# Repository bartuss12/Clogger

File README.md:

Clogger — Minimal Linux‑Powered USB eMMC Reader (F1C100S)
Clogger is a tiny, reproducible hardware project built around the Allwinner F1C100S, 
designed to read, clone, and analyze BGA153/BGA169 eMMC chips using nothing more than a Linux system running from an SD card. 
The goal is to create a fully open, hand‑solderable tool that exposes an attached eMMC device to a host PC over USB 
— just like a USB mass‑storage adapter, but built from scratch.

🔧 Goals

*Build a minimal F1C100S board that boots Linux entirely from an SD card

*Provide a UART‑accessible Linux shell for debugging and control

*Use USB gadget mode to expose the connected eMMC as a block device

*Support BGA153/BGA169 eMMC reballing using low‑cost stencils and solder paste

*Offer a fully reproducible Buildroot toolchain (U‑Boot + kernel + rootfs)

*Document the entire bring‑up process: boot flow, device tree, SD layout, and USB configuration

*Create a simple, reliable tool for eMMC backup, cloning, and recovery

29.12.2025 Work on first hardware version started

31.12.2025 Added 3D models, added LEDs (for work without terminal), added decoupling capacitors, added line resistors

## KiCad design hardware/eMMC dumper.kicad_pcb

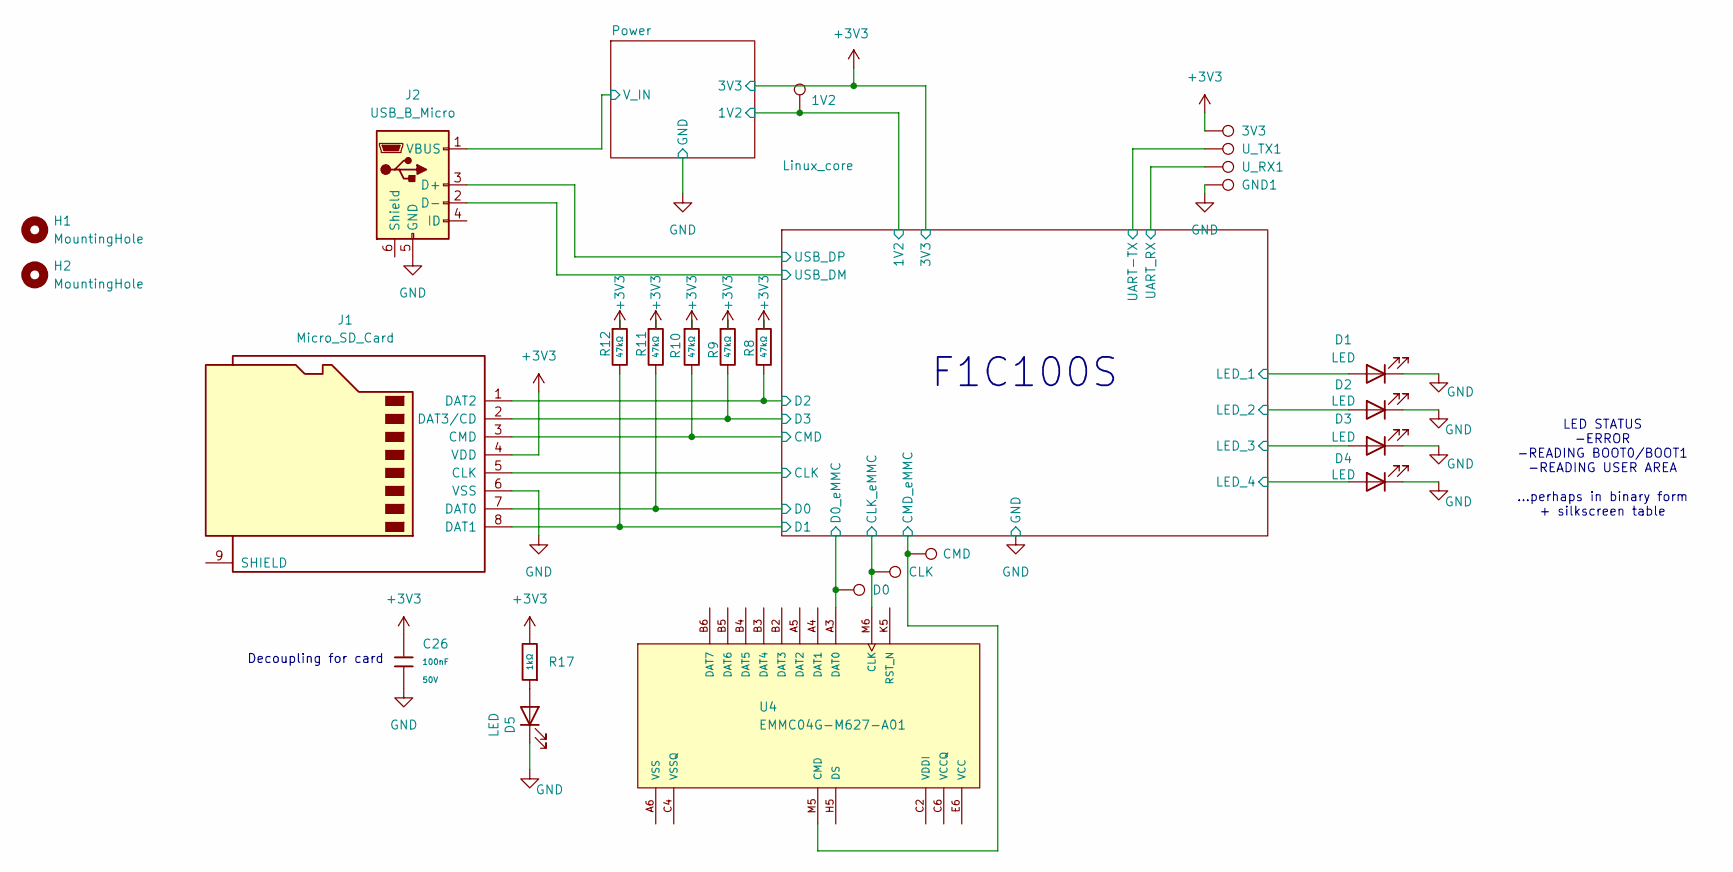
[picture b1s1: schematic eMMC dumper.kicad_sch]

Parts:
1V2, 3V3: TestPoint; TestPoint_Pad_D1.0mm
C26: 100nF; C_0603; Voltage Rated 50V; Tolerance ±10%; Part CC0603KRX7R9BB104; LCSC C14663
CLK: TestPoint; TestPoint_Pad_D1.0mm
CMD: TestPoint; TestPoint_Pad_D1.0mm
D0: TestPoint; TestPoint_Pad_D1.0mm
D1, D2, D3, D4, D5: LED; LED_0201_0603Metric
GND1: TestPoint; TestPoint_Pad_D1.0mm
H1, H2: MountingHole; MountingHole_3.2mm_M3
J1: Micro_SD_Card; microSD_HC_Molex_47219-2001
J2: USB_B_Micro; USB_Micro-AB_Molex_47590-0001
R8, R9, R10, R11, R12: 47kΩ; R_0402; Overload Voltage (Max) 50V; Tolerance ±1%; Part 0402WGF4702TCE; LCSC C25792
R17: 1kΩ; R_0603; Overload Voltage (Max) 75V; Tolerance ±1%; Part 0603WAF1001T5E; LCSC C21190
U4: EMMC04G-M627-A01; LFBGA-153_11.5x13mm_Layout14x14_P0.5mm; PART_REV 2.0
U_RX1: TestPoint; TestPoint_Pad_D1.0mm
U_TX1: TestPoint; TestPoint_Pad_D1.0mm

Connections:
+1V2: 1V2.1; also elsewhere on the board
+3V3: 3V3.1, C26.1, J1.4 (VDD), R8.1, R9.1, R10.1, R11.1, R12.1, R17.2; also elsewhere on the board
/Linux_core/CLK: J1.5 (CLK); also elsewhere on the board
/Linux_core/CLK_eMMC: CLK.1, U4.M6 (CLK); also elsewhere on the board
/Linux_core/CMD: J1.3 (CMD), R10.2; also elsewhere on the board
/Linux_core/CMD_eMMC: CMD.1, U4.M5 (CMD); also elsewhere on the board
/Linux_core/D0: J1.7 (DAT0), R11.2; also elsewhere on the board
/Linux_core/D0_eMMC: D0.1, U4.A3 (DAT0); also elsewhere on the board
/Linux_core/D1: J1.8 (DAT1), R12.2; also elsewhere on the board
/Linux_core/D2: J1.1 (DAT2), R8.2; also elsewhere on the board
/Linux_core/D3: J1.2 (DAT3/CD), R9.2; also elsewhere on the board
/Linux_core/LED_1: D1.2 (A); also elsewhere on the board
/Linux_core/LED_2: D2.2 (A); also elsewhere on the board
/Linux_core/LED_3: D3.2 (A); also elsewhere on the board
/Linux_core/LED_4: D4.2 (A); also elsewhere on the board
/Linux_core/UART-TX: U_TX1.1; also elsewhere on the board
/Linux_core/UART_RX: U_RX1.1; also elsewhere on the board
/Linux_core/USB_DM: J2.2 (D-); also elsewhere on the board
/Linux_core/USB_DP: J2.3 (D+); also elsewhere on the board
/Power/V_IN: J2.1 (VBUS); also elsewhere on the board
GND: C26.2, D1.1 (K), D2.1 (K), D3.1 (K), D4.1 (K), D5.1 (K), GND1.1, J1.6 (VSS), J2.5 (GND); also elsewhere on the board
unnamed: D5.2 (A), R17.1
VCC: U4.E6 (VCC), U4.F5 (VCC), U4.J10 (VCC), U4.K9 (VCC)
VCCQ: U4.C6 (VCCQ), U4.M4 (VCCQ), U4.N4 (VCCQ), U4.P3 (VCCQ), U4.P5 (VCCQ)
VSS: U4.A6 (VSS), U4.E7 (VSS), U4.G5 (VSS), U4.H10 (VSS), U4.J5 (VSS), U4.K8 (VSS)
VSSQ: U4.C4 (VSSQ), U4.N2 (VSSQ), U4.N5 (VSSQ), U4.P4 (VSSQ), U4.P6 (VSSQ)

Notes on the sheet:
LED STATUS -ERROR -READING BOOT0/BOOT1 -READING USER AREA ...perhaps in binary form + silkscreen table
Decoupling for card
F1C100S

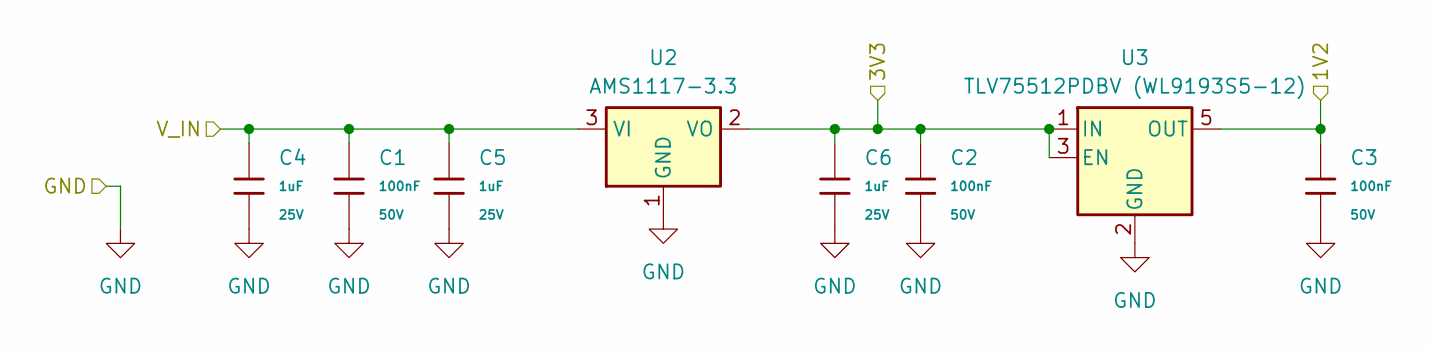
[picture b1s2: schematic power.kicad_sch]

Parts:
C1, C2, C3: 100nF; C_0603; Voltage Rated 50V; Tolerance ±10%; Part CC0603KRX7R9BB104; LCSC C14663
C4, C5, C6: 1uF; C_0402; Voltage Rated 25V; Tolerance ±10%; Part CL05A105KA5NQNC; LCSC C52923
U2: AMS1117-3.3; SOT-223-3_TabPin2
U3: TLV75512PDBV (WL9193S5-12); SOT-23-5

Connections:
+1V2: C3.1, U3.5 (OUT); also elsewhere on the board
+3V3: C2.1, C6.1, U2.2 (VO), U3.1 (IN), U3.3 (EN); also elsewhere on the board
/Power/V_IN: C1.1, C4.1, C5.1, U2.3 (VI); also elsewhere on the board
GND: C1.2, C2.2, C3.2, C4.2, C5.2, C6.2, U2.1 (GND), U3.2 (GND); also elsewhere on the board

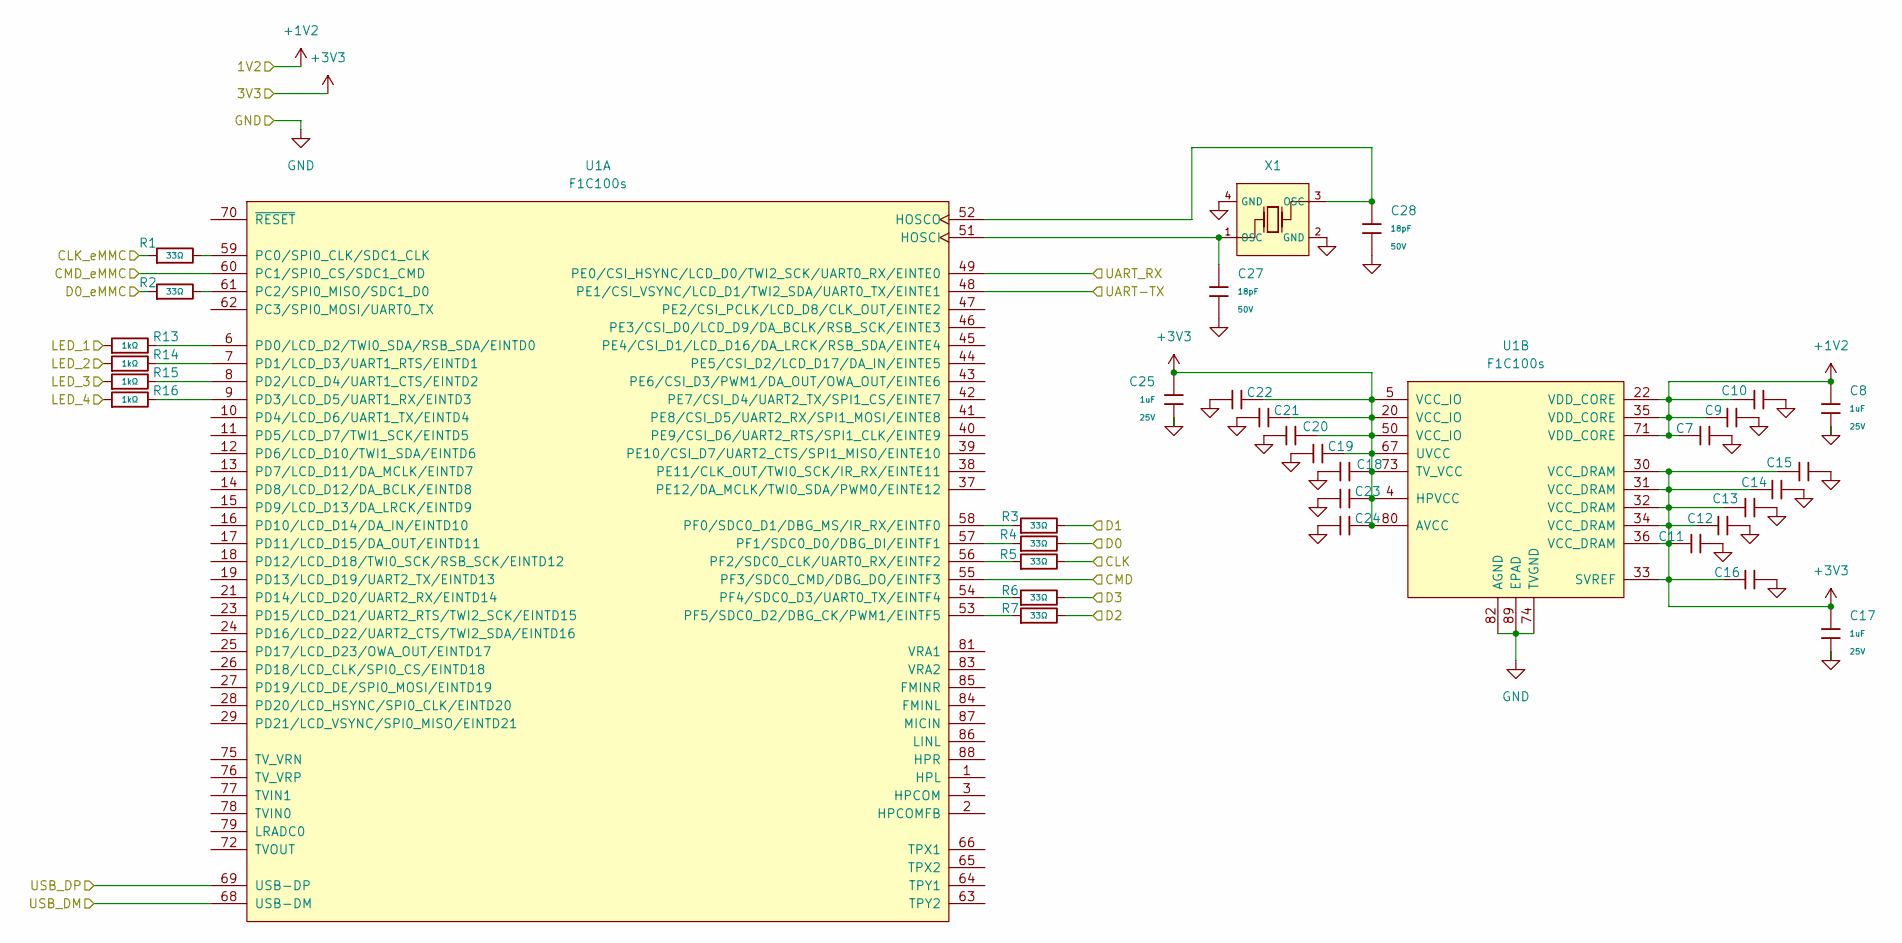
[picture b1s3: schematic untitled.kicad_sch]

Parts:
C7, C9, C10, C11, C12, C13, C14, C15, C16, C18, C19, C20, C21, C22, C23, C24: 100nF; C_0603; Voltage Rated 50V; Tolerance ±10%; Part CC0603KRX7R9BB104; LCSC C14663
C8, C17, C25: 1uF; C_0402; Voltage Rated 25V; Tolerance ±10%; Part CL05A105KA5NQNC; LCSC C52923
C27, C28: 18pF; C_0402; Voltage Rated 50V; Tolerance ±5%; Part 0402CG180J500NT; LCSC C1549
R1, R2, R3, R4, R5, R6, R7: 33Ω; R_0402; Overload Voltage (Max) 50V; Tolerance ±1%; Part 0402WGF330JTCE; LCSC C25105
R13, R14, R15, R16: 1kΩ; R_0603; Overload Voltage (Max) 75V; Tolerance ±1%; Part 0603WAF1001T5E; LCSC C21190
U1: F1C100s; ArtInChip_QFN-88-1EP_10x10mm_P0.4mm_EP6.74x6.74mm
X1: 24MHz; OSC-SMD_4P-L3.2-W2.5-BL; Frequency Tolerance ±10ppm; LCSC C2981673

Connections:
+1V2: C7.1, C8.1, C9.1, C10.1, U1.22 (VDD_CORE), U1.35 (VDD_CORE), U1.71 (VDD_CORE); also elsewhere on the board
+3V3: C11.1, C12.1, C13.1, C14.1, C15.1, C16.1, C17.1, C18.1, C19.1, C20.1, C21.1, C22.1, C23.1, C24.1, C25.1, U1.4 (HPVCC), U1.5 (VCC_IO), U1.20 (VCC_IO), U1.30 (VCC_DRAM), U1.31 (VCC_DRAM), U1.32 (VCC_DRAM), U1.33 (SVREF), U1.34 (VCC_DRAM), U1.36 (VCC_DRAM), U1.50 (VCC_IO), U1.67 (UVCC), U1.73 (TV_VCC), U1.80 (AVCC); also elsewhere on the board
/Linux_core/CLK: R5.2; also elsewhere on the board
/Linux_core/CLK_eMMC: R1.1; also elsewhere on the board
/Linux_core/CMD: U1.55 (PF3/SDC0_CMD/DBG_DO/EINTF3); also elsewhere on the board
/Linux_core/CMD_eMMC: U1.60 (PC1/SPI0_CS/SDC1_CMD); also elsewhere on the board
/Linux_core/D0: R4.2; also elsewhere on the board
/Linux_core/D0_eMMC: R2.1; also elsewhere on the board
/Linux_core/D1: R3.2; also elsewhere on the board
/Linux_core/D2: R7.2; also elsewhere on the board
/Linux_core/D3: R6.2; also elsewhere on the board
/Linux_core/LED_1: R13.1; also elsewhere on the board
/Linux_core/LED_2: R14.1; also elsewhere on the board
/Linux_core/LED_3: R15.1; also elsewhere on the board
/Linux_core/LED_4: R16.1; also elsewhere on the board
/Linux_core/UART-TX: U1.48 (PE1/CSI_VSYNC/LCD_D1/TWI2_SDA/UART0_TX/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); also elsewhere on the board
/Linux_core/UART_RX: U1.49 (PE0/CSI_HSYNC/LCD_D0/TWI2_SCK/UART0_RX/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); also elsewhere on the board
/Linux_core/USB_DM: U1.68 (USB-DM); also elsewhere on the board
/Linux_core/USB_DP: U1.69 (USB-DP); also elsewhere on the board
GND: C7.2, C8.2, C9.2, C10.2, C11.2, C12.2, C13.2, C14.2, C15.2, C16.2, C17.2, C18.2, C19.2, C20.2, C21.2, C22.2, C23.2, C24.2, C25.2, C27.2, C28.2, U1.74 (TVGND), U1.82 (AGND), U1.89 (EPAD), X1.2 (GND), X1.4 (GND); also elsewhere on the board
unnamed: C27.1, U1.51 (HOSCI), X1.1 (OSC)
unnamed: C28.1, U1.52 (HOSCO), X1.3 (OSC)
unnamed: R1.2, U1.59 (PC0/SPI0_CLK/SDC1_CLK)
unnamed: R2.2, U1.61 (PC2/SPI0_MISO/SDC1_D0)
unnamed: R13.2, U1.6 (PD0/LCD_D2/TWI0_SDA/RSB_SDA/EINTD0)
unnamed: R14.2, U1.7 (PD1/LCD_D3/UART1_RTS/EINTD1)
unnamed: R15.2, U1.8 (PD2/LCD_D4/UART1_CTS/EINTD2)
unnamed: R16.2, U1.9 (PD3/LCD_D5/UART1_RX/EINTD3)
unnamed: R3.1, U1.58 (PF0/SDC0_D1/DBG_MS/IR_RX/EINTF0)
unnamed: R4.1, U1.57 (PF1/SDC0_D0/DBG_DI/EINTF1)
unnamed: R5.1, U1.56 (PF2/SDC0_CLK/UART0_RX/EINTF2)
unnamed: R6.1, U1.54 (PF4/SDC0_D3/UART0_TX/EINTF4)
unnamed: R7.1, U1.53 (PF5/SDC0_D2/DBG_CK/PWM1/EINTF5)

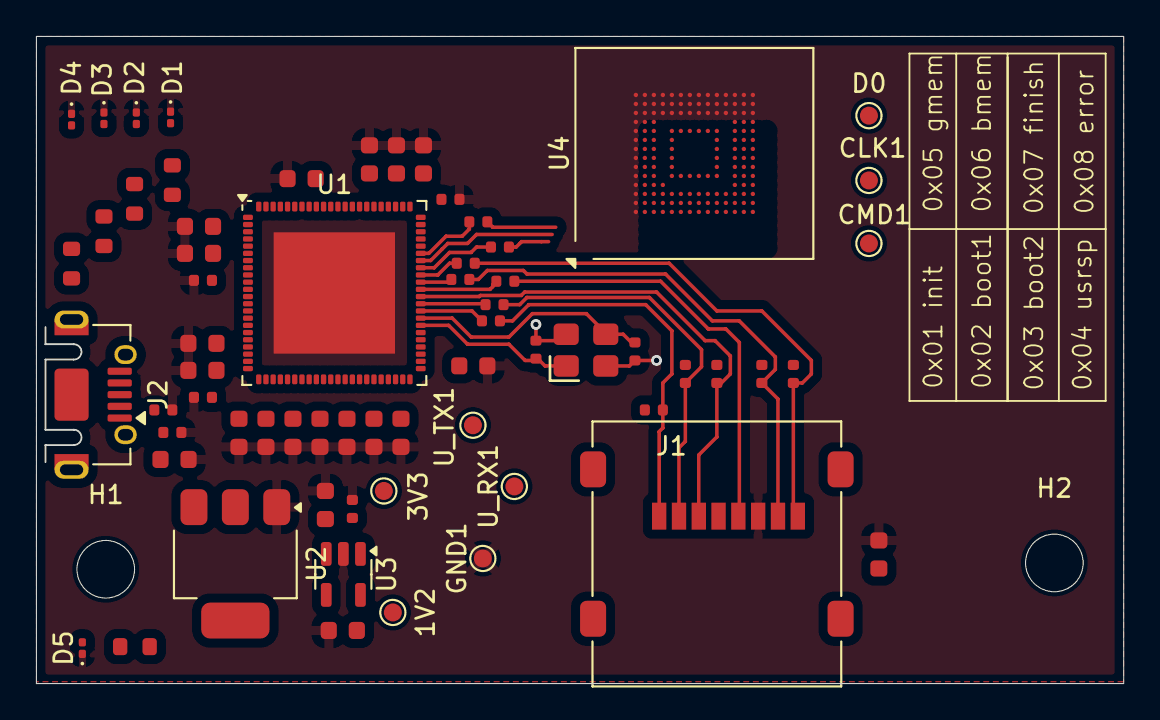
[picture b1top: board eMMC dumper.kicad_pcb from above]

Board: 2 copper layers, 60.3 x 35.9 mm, 67 parts (0 on the bottom side), 39 nets.

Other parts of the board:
CLK1: TestPoint; TestPoint_Pad_D1.0mm
CMD1: TestPoint; TestPoint_Pad_D1.0mm

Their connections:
/Linux_core/CLK_eMMC: CLK1.1; also elsewhere on the board
/Linux_core/CMD_eMMC: CMD1.1; also elsewhere on the board

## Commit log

2017-01-02 :octocat: Added .gitattributes & .gitignore files
2017-01-02 First version of code
    -reading signals after button is pushed
    -sending signal after other button is pushed
2025-12-26 Rename uboot_2009-08-lab126_wario_stock_bist (1).bin to uboot.bin
2025-12-28 Initialize README with project description and goals
    Added project overview and goals for Clogger.
2025-12-29 Revert "Add files via upload"
    This reverts commit 3901323e0dd8efd3fd20ebb9b2ae35cccd248ec9.
2025-12-29 Revert "Add files via upload"
    This reverts commit ba332ca235fc481233c32f59f4eb52eb91161519.
2025-12-29 clean up
2025-12-29 Added hw project
2025-12-29 Basic schematic
    Need to add passives
2025-12-29 added data/clk resistors (33ohm)
2025-12-29 Added core decoupling caps
2025-12-29 Added pullups for SD card
2025-12-29 Board design started
2025-12-30 Started placing decoupling capacitors
2025-12-31 PCB major changes
2026-01-02 Moved LEDs, renamed testpoints
2026-01-02 added quartz
2026-01-02 Moved some parts, started routing
